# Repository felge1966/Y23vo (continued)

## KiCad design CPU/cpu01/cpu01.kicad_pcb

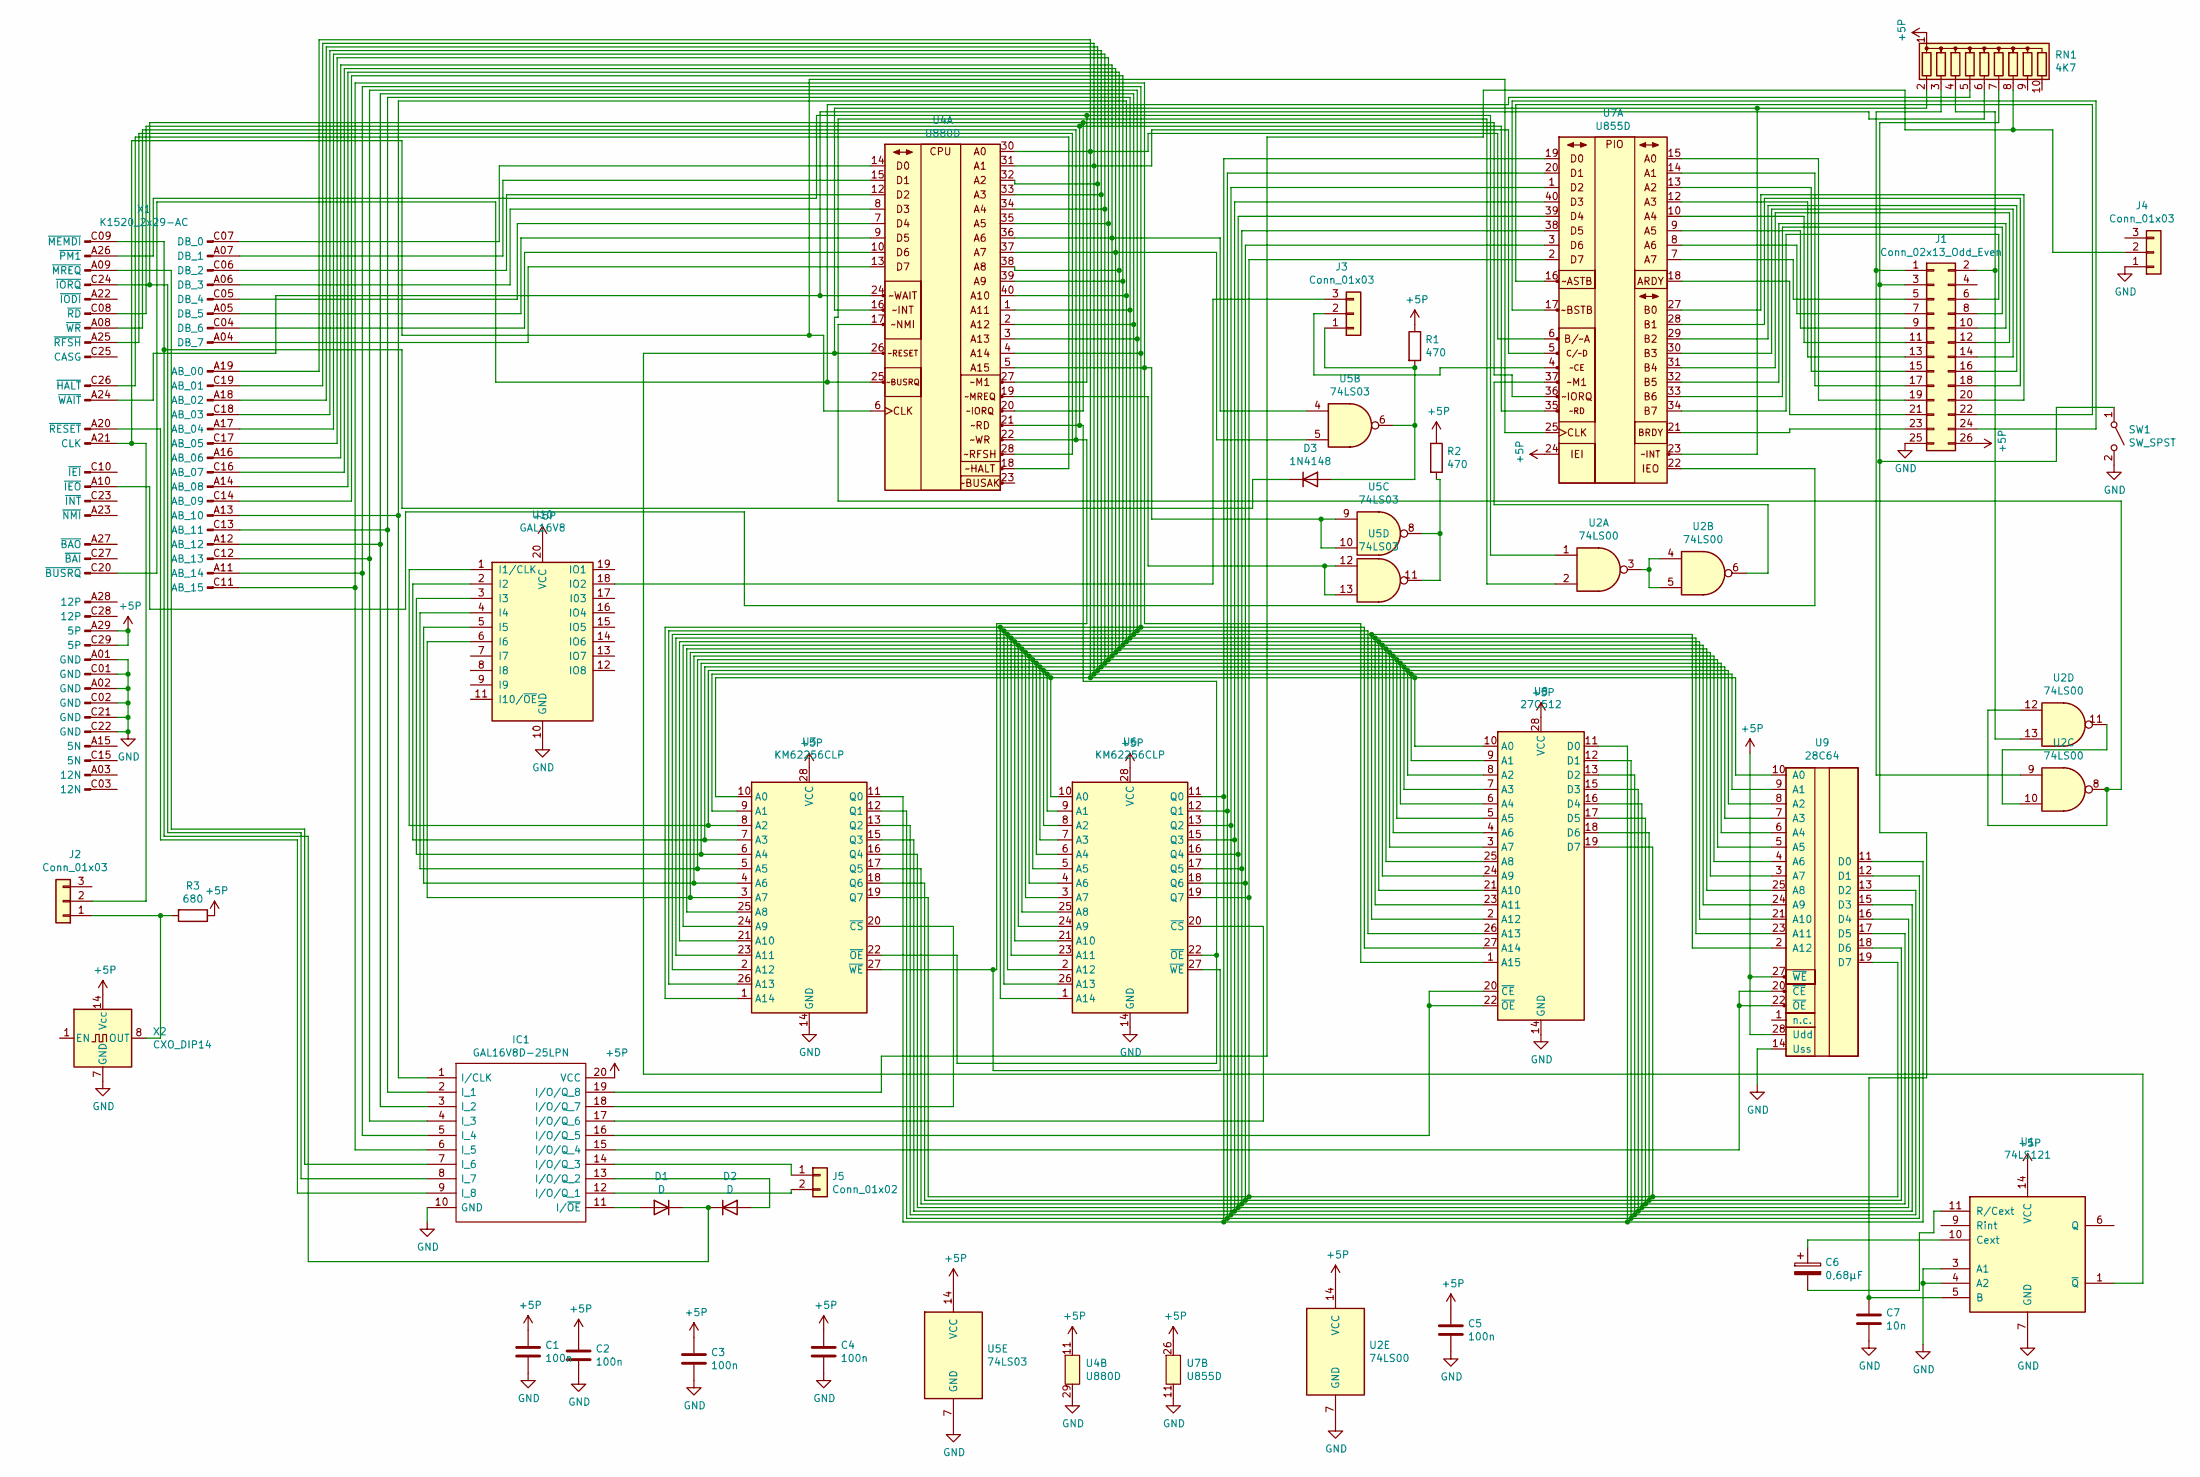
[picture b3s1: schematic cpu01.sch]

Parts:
C1, C2, C3, C4, C5: 100n; C_Disc_D3.0mm_W2.0mm_P2.50mm
C6: 0,68µF; CP_Radial_D4.0mm_P2.00mm
C7: 10n; C_Disc_D3.0mm_W2.0mm_P2.50mm
D1, D2: D; D_DO-15_P10.16mm_Horizontal
D3: 1N4148; D_DO-15_P10.16mm_Horizontal
IC1: GAL16V8D-25LPN; DIP762W56P254L2591H533Q20N; Manufacturer_Part_Number GAL16V8D-25LPN; Mouser Part Number 842-GAL16V8D25LPN
J1: Conn_02x13_Odd_Even; PinSocket_2x13_P2.54mm_Horizontal
J2, J3, J4: Conn_01x03; PinSocket_1x03_P2.54mm_Vertical
J5: Conn_01x02; PinSocket_1x02_P2.54mm_Vertical
R1, R2: 470; R_Axial_DIN0207_L6.3mm_D2.5mm_P10.16mm_Horizontal
R3: 680; R_Axial_DIN0207_L6.3mm_D2.5mm_P10.16mm_Horizontal
RN1: 4K7; R_Array_SIP10
SW1: SW_SPST; SW_Tactile_SKHH_Angled
U1: 74LS121; DIP-14_W7.62mm_LongPads
U2: 74LS00; DIP-14_W7.62mm_LongPads
U3, U6: KM62256CLP; DIP-28_W15.24mm
U4: U880D; DIP-40_W15.24mm_LongPads
U5: 74LS03; DIP-14_W7.62mm_LongPads
U7: U855D; DIP-40_W15.24mm_LongPads
U8: 27C512; DIP-28_W15.24mm
U9: 28C64; DIP-28_W15.24mm_LongPads
U10: GAL16V8; PLCC-20_THT-Socket
X1: K1520_2x29-AC; K1520_EFS2x29_DIN_male
X2: CXO_DIP14; Oscillator_DIP-14

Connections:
+5P: C1.1, C2.1, C3.1, C4.1, C5.1, IC1.20 (VCC), J1.26, R1.1, R2.1, R3.1, RN1.1 (common), U1.14 (VCC), U2.14 (VCC), U3.28 (VCC), U4.11 (Vcc), U5.14 (VCC), U6.28 (VCC), U7.24 (IEI), U7.26 (Vcc), U8.28 (VCC), U9.27 (~WE), U9.28 (Udd), U10.20 (VCC), X1.A29 (5P), X1.C29 (5P), X2.14 (Vcc)
GND: C1.2, C2.2, C3.2, C4.2, C5.2, C7.2, IC1.10 (GND), J1.25, J4.1, SW1.2 (B), U1.3 (A1), U1.4 (A2), U1.7 (GND), U2.7 (GND), U3.14 (GND), U4.29 (GND), U5.7 (GND), U6.14 (GND), U7.11 (GND), U8.14 (GND), U9.14 (Uss), U10.10 (GND), X1.A01 (GND), X1.A02 (GND), X1.C01 (GND), X1.C02 (GND), X1.C21 (GND), X1.C22 (GND), X2.7 (GND)
unnamed: C6.1, U1.10 (Cext)
unnamed: C6.2, U1.11 (R/Cext)
unnamed: C7.1, J1.3, RN1.7 (R6), SW1.1 (A), U1.5 (B)
unnamed: D1.1 (K), D2.1 (K), D3.1 (K), X1.C09 (~MEMDI)
unnamed: D1.2 (A), IC1.11 (I/~OE)
unnamed: D2.2 (A), IC1.13 (I/O/Q_2)
unnamed: D3.2 (A), J3.1, R1.2, U5.6
unnamed: IC1.1 (I/CLK), U3.21 (A10), U4.40 (A10), U6.21 (A10), U8.21 (A10), U9.21 (A10), X1.A13 (AB_10)
unnamed: IC1.2 (I_1), U3.23 (A11), U4.1 (A11), U6.23 (A11), U8.23 (A11), U9.23 (A11), X1.C13 (AB_11)
unnamed: IC1.3 (I_2), U3.2 (A12), U4.2 (A12), U6.2 (A12), U8.2 (A12), U9.2 (A12), X1.A12 (AB_12)
unnamed: IC1.4 (I_3), U3.26 (A13), U4.3 (A13), U6.26 (A13), U8.26 (A13), X1.C12 (AB_13)
unnamed: IC1.5 (I_4), U3.1 (A14), U4.4 (A14), U6.1 (A14), U8.27 (A14), X1.A11 (AB_14)
unnamed: IC1.6 (I_5), U4.5 (A15), U5.9, U5.10, U8.1 (A15), X1.C11 (AB_15)
unnamed: IC1.7 (I_6), X1.A09 (~MREQ)
unnamed: IC1.8 (I_7), U4.20 (~IORQ), U7.36 (~IORQ), X1.C24 (~IORQ)
unnamed: IC1.9 (I_8), X1.A20 (~RESET)
unnamed: IC1.12 (I/O/Q_1), J5.2
unnamed: IC1.14 (I/O/Q_3), J5.1
unnamed: IC1.15 (I/O/Q_4), U9.20 (~CE), U9.22 (~OE)
unnamed: IC1.16 (I/O/Q_5), U8.20 (~CE), U8.22 (~OE)
unnamed: IC1.17 (I/O/Q_6), U6.20 (~CS)
unnamed: IC1.18 (I/O/Q_7), U3.20 (~CS)
unnamed: IC1.19 (I/O/Q_8), J4.2, RN1.8 (R7)
unnamed: J1.1, RN1.3 (R2), U2.9
unnamed: J1.2, RN1.4 (R3), U2.13
unnamed: J1.5, U7.7 (A7)
unnamed: J1.6, U7.34 (B7)
unnamed: J1.7, U7.8 (A6)
unnamed: J1.8, U7.33 (B6)
unnamed: J1.9, U7.9 (A5)
unnamed: J1.10, U7.32 (B5)
unnamed: J1.11, U7.10 (A4)
unnamed: J1.12, U7.31 (B4)
unnamed: J1.13, U7.12 (A3)
unnamed: J1.14, U7.30 (B3)
unnamed: J1.15, U7.13 (A2)
unnamed: J1.16, U7.29 (B2)
unnamed: J1.17, U7.14 (A1)
unnamed: J1.18, U7.28 (B1)
unnamed: J1.19, U7.15 (A0)
unnamed: J1.20, U7.27 (B0)
unnamed: J1.21, U7.18 (ARDY)
unnamed: J1.22, U7.16 (~ASTB)
unnamed: J1.23, U7.21 (BRDY)
unnamed: J1.24, U7.17 (~BSTB)
unnamed: J2.1, R3.2, X2.8 (OUT)
unnamed: J2.2, U4.6 (CLK), U7.25 (CLK), X1.A21 (CLK)
unnamed: J3.2, U7.4 (~CE)
unnamed: J3.3, U10.18 (IO2)
unnamed: R2.2, U5.8, U5.11
unnamed: RN1.2 (R1), U4.16 (~INT), U7.23 (~INT)
unnamed: RN1.5 (R4), U4.25 (~BUSRQ), X1.C20 (~BUSRQ)
unnamed: RN1.6 (R5), U4.24 (~WAIT), X1.A24 (~WAIT)
unnamed: U1.1 (~Q), U2.2, U4.26 (~RESET)
unnamed: U2.1, U4.27 (~M1), X1.A26 (~PM1)
unnamed: U2.3, U2.4, U2.5
unnamed: U2.6, U7.37 (~M1)
unnamed: U2.10, U2.11
unnamed: U2.8, U2.12, U4.17 (~NMI)
unnamed: U3.9 (A1), U4.31 (A1), U6.9 (A1), U7.5 (C/~D), U8.9 (A1), U9.9 (A1), X1.C19 (AB_01)
unnamed: U3.10 (A0), U4.30 (A0), U6.10 (A0), U7.6 (B/~A), U8.10 (A0), U9.10 (A0), X1.A19 (AB_00)
unnamed: U3.11 (Q0), U6.11 (Q0), U7.19 (D0), U8.11 (D0), U9.11 (D0)
unnamed: U3.12 (Q1), U6.12 (Q1), U7.20 (D1), U8.12 (D1), U9.12 (D1)
unnamed: U3.13 (Q2), U6.13 (Q2), U7.1 (D2), U8.13 (D2), U9.13 (D2)
unnamed: U3.15 (Q3), U6.15 (Q3), U7.40 (D3), U8.15 (D3), U9.15 (D3)
unnamed: U3.16 (Q4), U6.16 (Q4), U7.39 (D4), U8.16 (D4), U9.16 (D4)
unnamed: U3.17 (Q5), U6.17 (Q5), U7.38 (D5), U8.17 (D5), U9.17 (D5)
unnamed: U3.18 (Q6), U6.18 (Q6), U7.3 (D6), U8.18 (D6), U9.18 (D6)
unnamed: U3.19 (Q7), U6.19 (Q7), U7.2 (D7), U8.19 (D7), U9.19 (D7)
unnamed: U3.22 (~OE), U4.21 (~RD), U6.22 (~OE), U7.35 (~RD), X1.C08 (~RD)
unnamed: U3.24 (A9), U4.39 (A9), U6.24 (A9), U8.24 (A9), U9.24 (A9), X1.C14 (AB_09)
unnamed: U3.25 (A8), U4.38 (A8), U6.25 (A8), U8.25 (A8), U9.25 (A8), X1.A14 (AB_08)
unnamed: U3.27 (~WE), U4.22 (~WR), U6.27 (~WE), X1.A08 (~WR)
unnamed: U4.7 (D4), X1.C05 (DB_4)
unnamed: U4.8 (D3), X1.A06 (DB_3)
unnamed: U4.9 (D5), X1.A05 (DB_5)
unnamed: U4.10 (D6), X1.C04 (DB_6)
unnamed: U4.12 (D2), X1.C06 (DB_2)
unnamed: U4.13 (D7), X1.A04 (DB_7)
unnamed: U4.14 (D0), X1.C07 (DB_0)
unnamed: U4.15 (D1), X1.A07 (DB_1)
unnamed: U4.18 (~HALT), X1.C26 (~HALT)
unnamed: U4.19 (~MREQ), U5.12, U5.13
unnamed: U4.28 (~RFSH), X1.A25 (~RFSH)
unnamed: U7.22 (IEO), X1.A10 (~IEO)
unnamed: U3.8 (A2), U4.32 (A2), U6.8 (A2), U8.8 (A2), U9.8 (A2), U10.1 (I1/CLK), X1.A18 (AB_02)
unnamed: U3.7 (A3), U4.33 (A3), U6.7 (A3), U8.7 (A3), U9.7 (A3), U10.2 (I2), X1.C18 (AB_03)
unnamed: U3.6 (A4), U4.34 (A4), U6.6 (A4), U8.6 (A4), U9.6 (A4), U10.3 (I3), X1.A17 (AB_04)
unnamed: U3.5 (A5), U4.35 (A5), U6.5 (A5), U8.5 (A5), U9.5 (A5), U10.4 (I4), X1.C17 (AB_05)
unnamed: U3.4 (A6), U4.36 (A6), U5.4, U6.4 (A6), U8.4 (A6), U9.4 (A6), U10.5 (I5), X1.A16 (AB_06)
unnamed: U3.3 (A7), U4.37 (A7), U5.5, U6.3 (A7), U8.3 (A7), U9.3 (A7), U10.6 (I6), X1.C16 (AB_07)

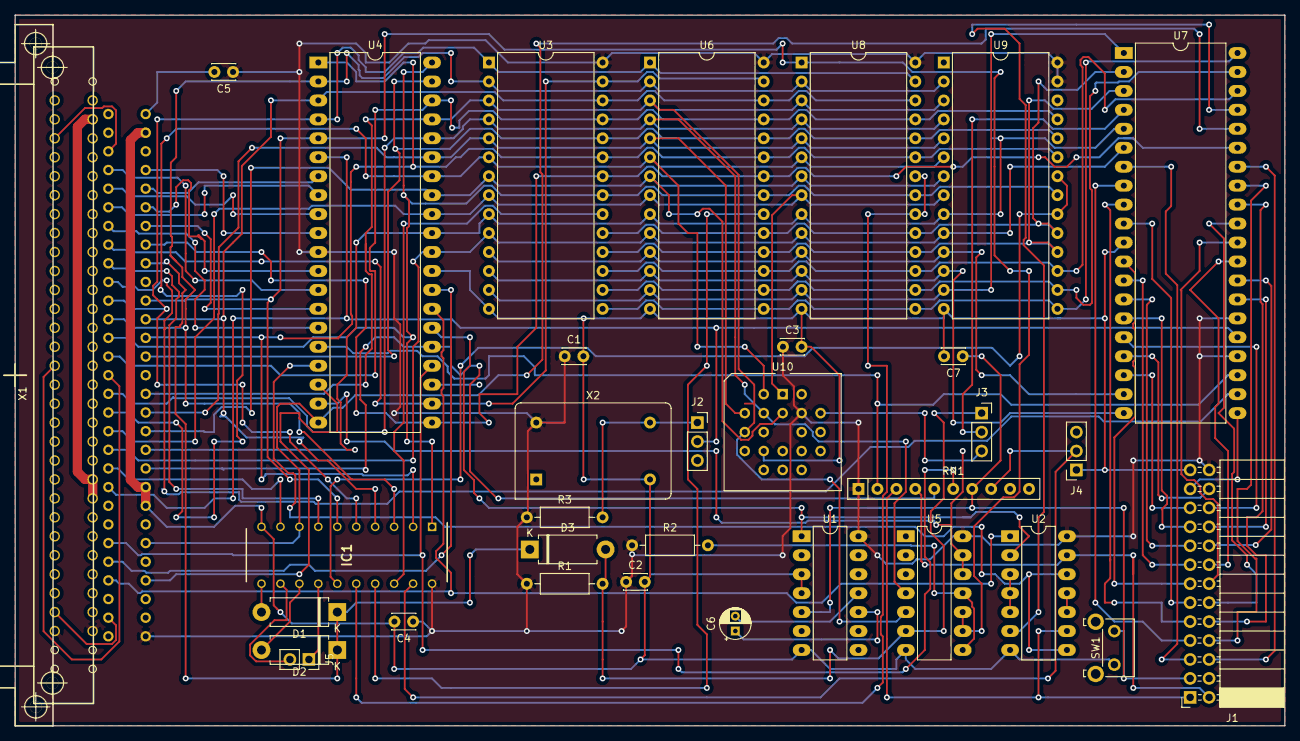
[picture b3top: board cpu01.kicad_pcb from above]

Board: 2 copper layers, 170.2 x 95.2 mm, 33 parts (0 on the bottom side), 93 nets.

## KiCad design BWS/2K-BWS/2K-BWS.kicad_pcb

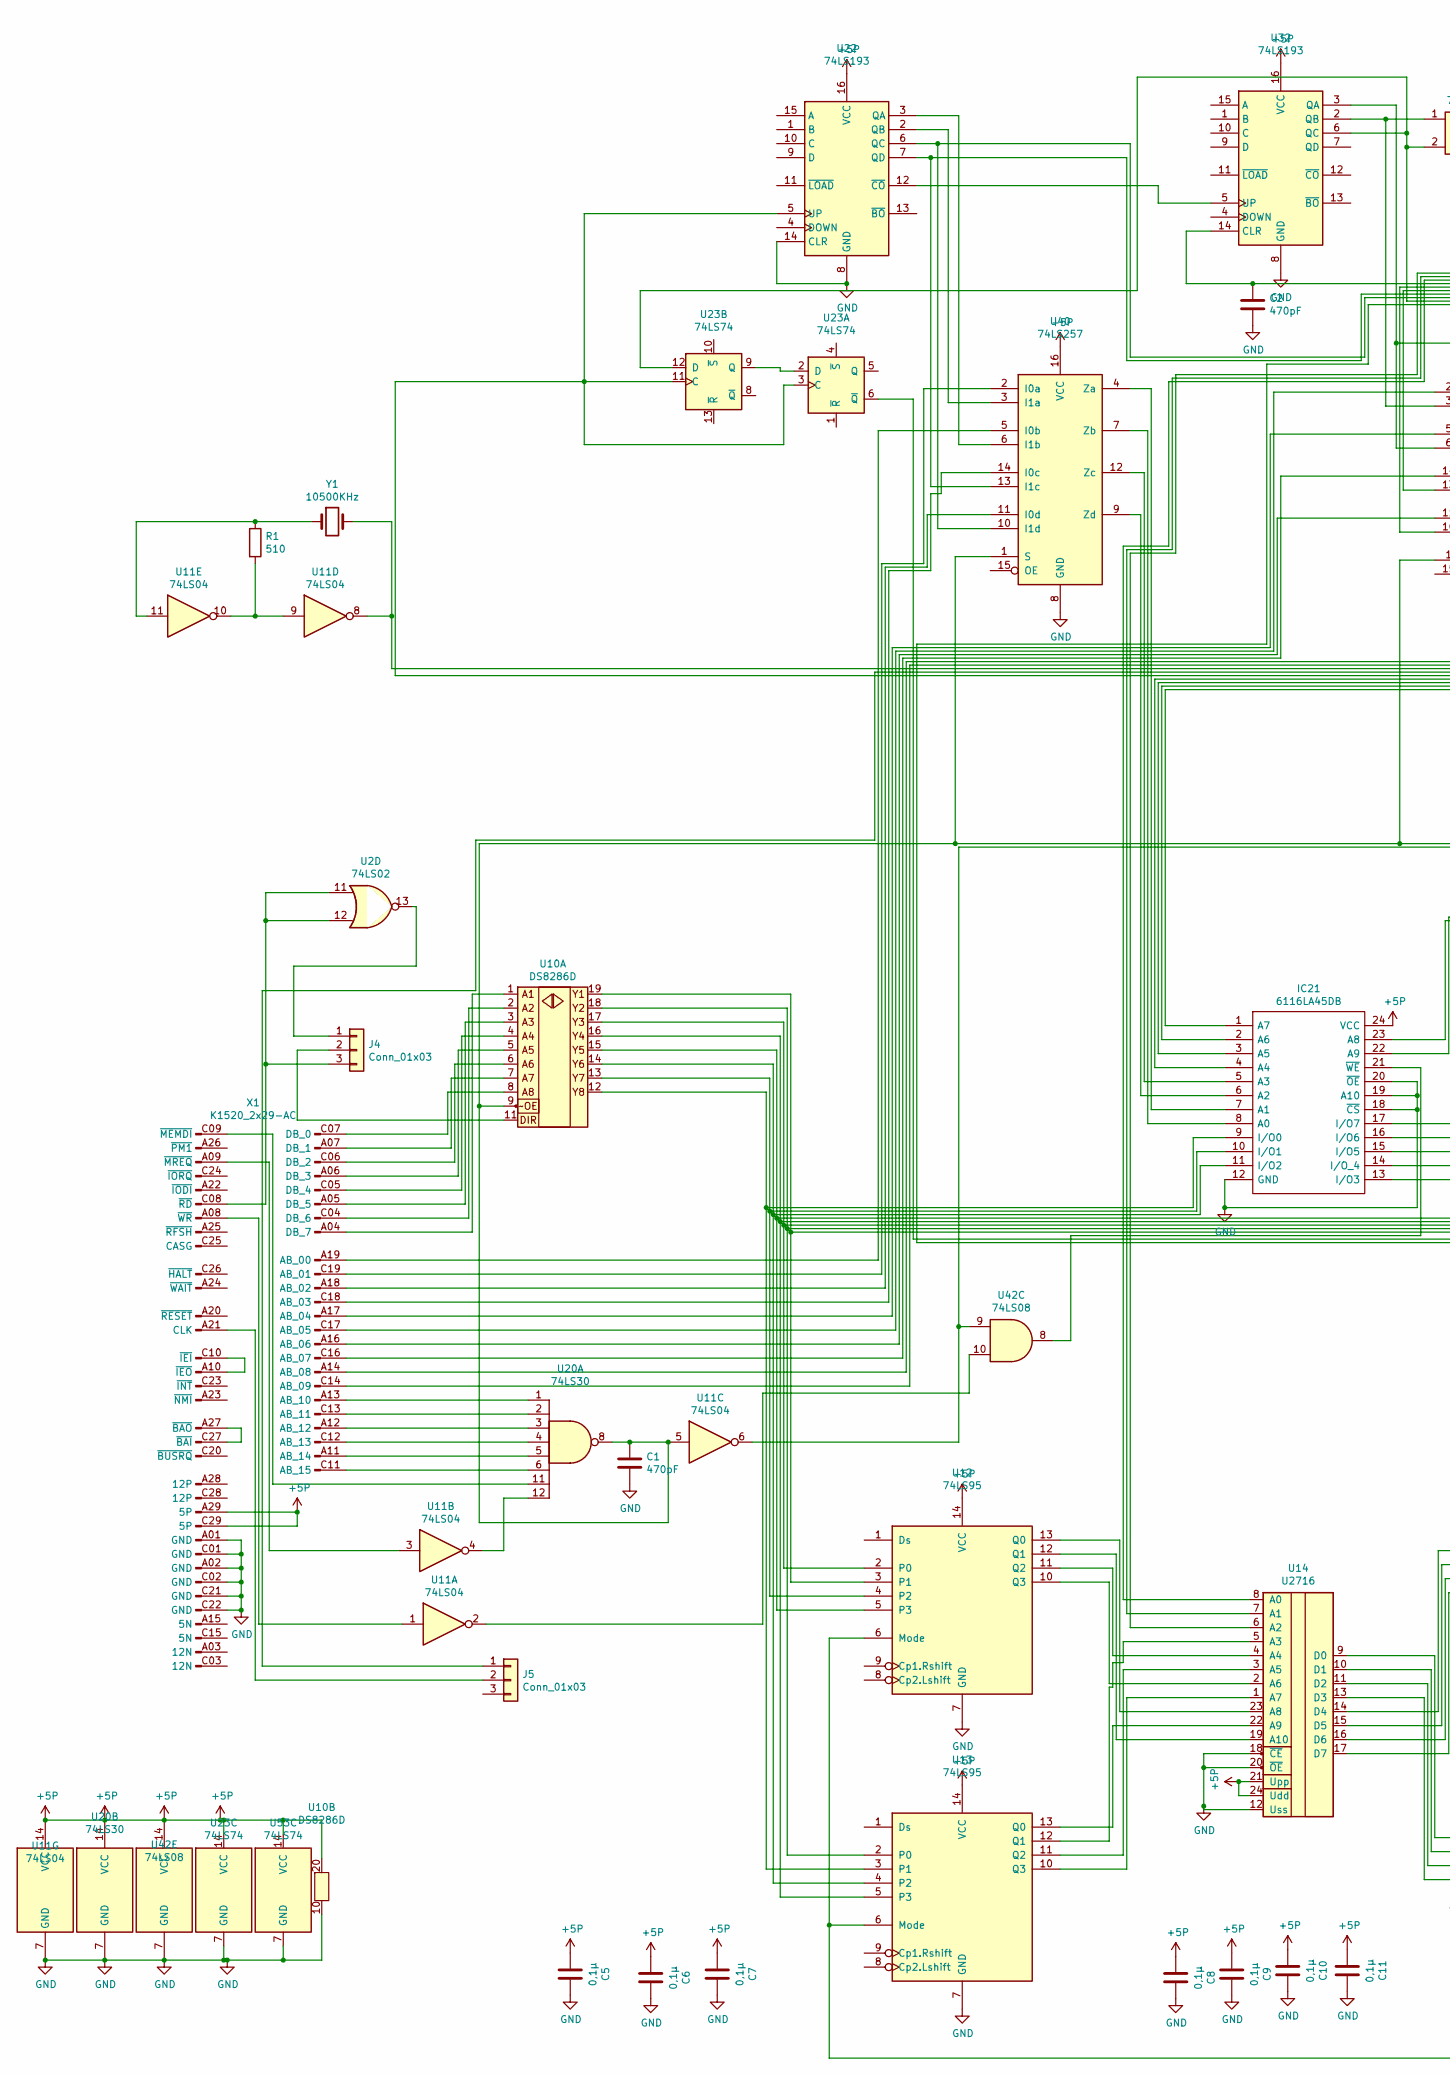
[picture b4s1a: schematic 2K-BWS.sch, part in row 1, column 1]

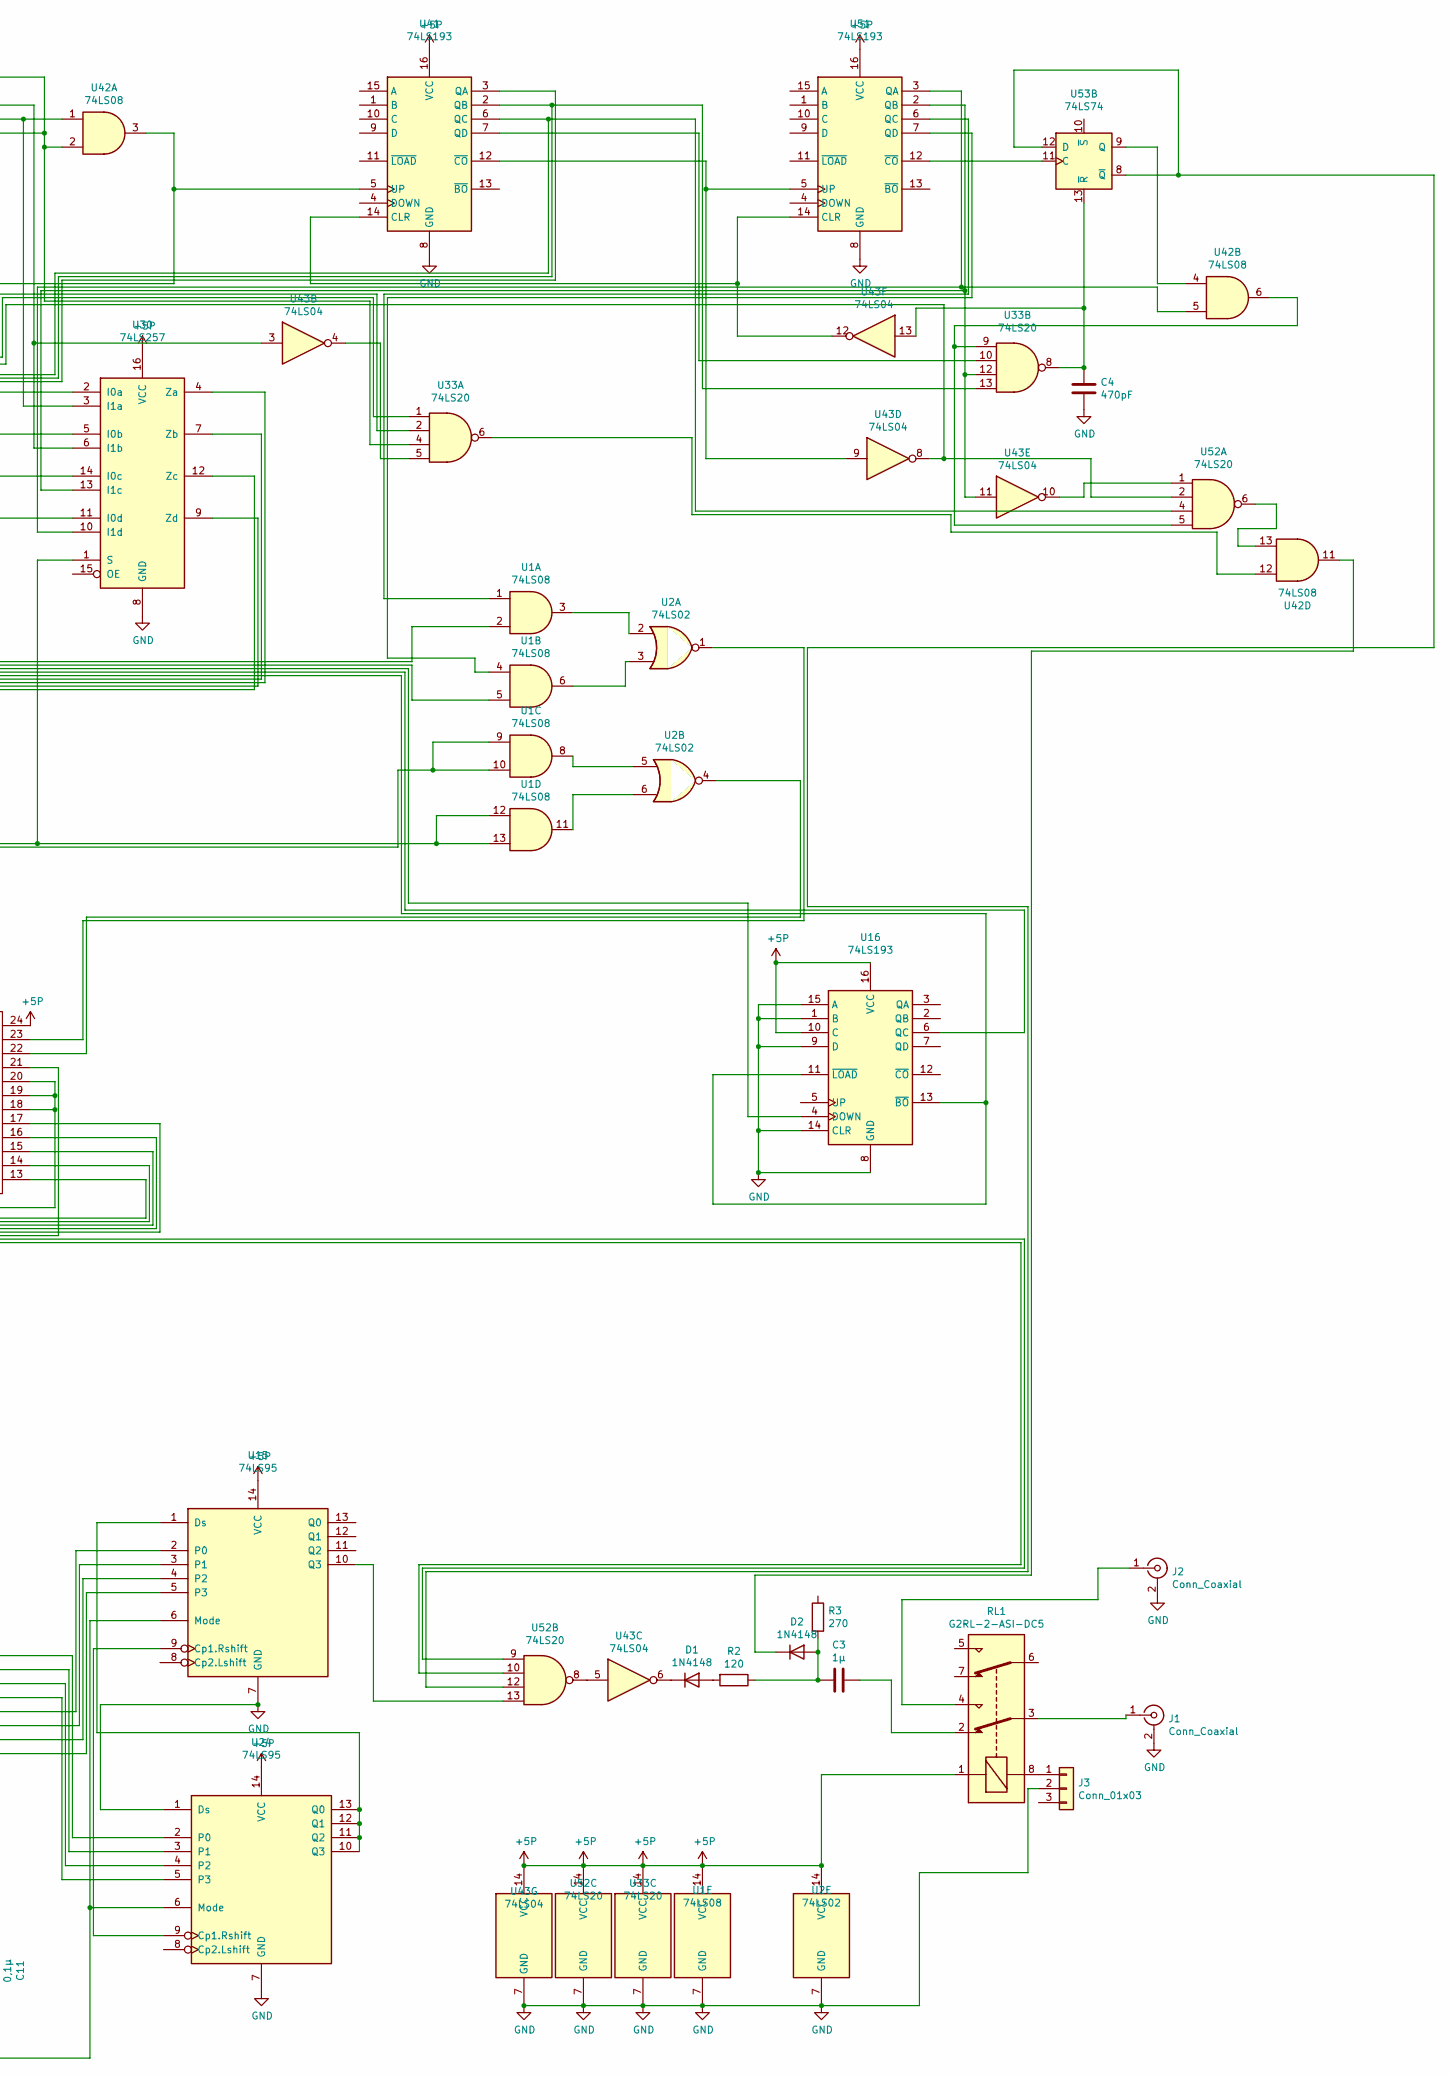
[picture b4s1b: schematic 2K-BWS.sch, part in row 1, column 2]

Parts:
C1, C2, C4: 470pF; C_Disc_D3.0mm_W2.0mm_P2.50mm
C3: 1µ; C_Disc_D3.0mm_W2.0mm_P2.50mm
C5, C6, C7, C8, C9, C10, C11: 0,1µ; C_Disc_D3.0mm_W2.0mm_P2.50mm
D1, D2: 1N4148; D_DO-15_P10.16mm_Horizontal
IC21: 6116LA45DB; DIP-24_W15.24mm_LongPads; Manufacturer_Part_Number 6116LA45DB; Mouser Part Number 972-6116LA45DB
J1, J2: Conn_Coaxial; chinch
J3, J4, J5: Conn_01x03; PinSocket_1x03_P2.54mm_Vertical
R1: 510; R_Axial_DIN0207_L6.3mm_D2.5mm_P10.16mm_Horizontal
R2: 120; R_Axial_DIN0207_L6.3mm_D2.5mm_P10.16mm_Horizontal
R3: 270; R_Axial_DIN0207_L6.3mm_D2.5mm_P10.16mm_Horizontal
RL1: G2RL-2-ASI-DC5; Relay_DPDT_Omron_G2RL
U1, U42: 74LS08; DIP-14_W7.62mm_LongPads
U2: 74LS02; DIP-14_W7.62mm_LongPads
U10: DS8286D; DIP-20_W7.62mm_LongPads
U11, U43: 74LS04; DIP-14_W7.62mm_LongPads
U12, U13, U15, U24: 74LS95; DIP-14_W7.62mm_LongPads
U14: U2716; DIP-24_W15.24mm_LongPads
U16, U22, U32, U41, U51: 74LS193; DIP-16_W7.62mm_LongPads
U20: 74LS30; DIP-14_W7.62mm_LongPads
U23, U53: 74LS74; DIP-14_W7.62mm_LongPads
U30, U40: 74LS257; DIP-16_W7.62mm_LongPads
U33, U52: 74LS20; DIP-14_W7.62mm_LongPads
X1: K1520_2x29-AC; K1520_EFS2x29_DIN_male
Y1: 10500KHz; Crystal_HC49-4H_Vertical

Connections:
+5P: C5.2, C6.2, C7.2, C8.2, C9.2, C10.2, C11.2, IC21.24 (VCC), RL1.1, U1.14 (VCC), U2.14 (VCC), U10.20 (Vcc), U11.14 (VCC), U12.14 (VCC), U13.14 (VCC), U14.21 (Upp), U14.24 (Udd), U15.14 (VCC), U16.10 (C), U16.16 (VCC), U20.14 (VCC), U22.16 (VCC), U23.14 (VCC), U24.14 (VCC), U30.16 (VCC), U32.16 (VCC), U33.14 (VCC), U40.16 (VCC), U41.16 (VCC), U42.14 (VCC), U43.14 (VCC), U51.16 (VCC), U52.14 (VCC), U53.14 (VCC), X1.A29 (5P), X1.C29 (5P)
GND: C1.2, C2.2, C4.2, C5.1, C6.1, C7.1, C8.1, C9.1, C10.1, C11.1, IC21.12 (GND), IC21.18 (~CS), IC21.19 (A10), IC21.20 (~OE), J1.2 (Ext), J2.2 (Ext), J3.2, U1.7 (GND), U2.7 (GND), U10.10 (GND), U11.7 (GND), U12.7 (GND), U13.7 (GND), U14.12 (Uss), U14.18 (~CE), U14.20 (~OE), U15.7 (GND), U16.1 (B), U16.8 (GND), U16.9 (D), U16.14 (CLR), U16.15 (A), U20.7 (GND), U22.8 (GND), U22.14 (CLR), U23.7 (GND), U24.1 (Ds), U24.7 (GND), U30.8 (GND), U32.8 (GND), U33.7 (GND), U40.8 (GND), U41.8 (GND), U42.7 (GND), U43.7 (GND), U51.8 (GND), U52.7 (GND), U53.7 (GND), X1.A01 (GND), X1.A02 (GND), X1.C01 (GND), X1.C02 (GND), X1.C21 (GND), X1.C22 (GND)
unnamed: C1.1, U1.12, U1.13, U10.9 (~OE), U11.5, U20.8, U30.1 (S), U40.1 (S)
unnamed: C2.1, U32.14 (CLR), U41.5 (UP), U42.3
unnamed: C3.1, RL1.2
unnamed: C3.2, D2.2 (A), R2.1, R3.2
unnamed: C4.1, U33.8, U43.13, U53.13 (~R)
unnamed: D1.1 (K), U43.6
unnamed: D1.2 (A), R2.2
unnamed: D2.1 (K), U42.11
unnamed: IC21.1 (A7), U30.12 (Zc)
unnamed: IC21.2 (A6), U30.9 (Zd)
unnamed: IC21.3 (A5), U30.4 (Za)
unnamed: IC21.4 (A4), U30.7 (Zb)
unnamed: IC21.5 (A3), U40.12 (Zc)
unnamed: IC21.6 (A2), U40.9 (Zd)
unnamed: IC21.7 (A1), U40.4 (Za)
unnamed: IC21.8 (A0), U40.7 (Zb)
unnamed: IC21.9 (I/O0), U10.12 (Y8), U13.3 (P1)
unnamed: IC21.10 (I/O1), U10.13 (Y7), U12.4 (P2)
unnamed: IC21.11 (I/O2), U10.14 (Y6), U13.4 (P2)
unnamed: IC21.13 (I/O3), U10.15 (Y5), U12.5 (P3)
unnamed: IC21.14 (I/O_4), U10.16 (A4), U13.5 (P3)
unnamed: IC21.15 (I/O5), U10.17 (Y3), U12.2 (P0)
unnamed: IC21.16 (I/O6), U10.18 (Y2), U13.2 (P0)
unnamed: IC21.17 (I/O7), U10.19 (Y1), U12.3 (P1)
unnamed: IC21.21 (~WE), U42.8
unnamed: IC21.22 (A9), U2.4
unnamed: IC21.23 (A8), U2.1
unnamed: J1.1 (In), RL1.3
unnamed: J2.1 (In), RL1.4
unnamed: J3.1, RL1.8
unnamed: J4.1, U2.13
unnamed: J4.2, U10.11 (STB)
unnamed: J4.3, U2.11, U2.12, X1.C08 (~RD)
unnamed: J5.1, U16.6 (QC)
unnamed: J5.2, X1.A21 (CLK)
unnamed: R1.1, U11.11, Y1.1
unnamed: R1.2, U11.9, U11.10
unnamed: U1.1, U51.6 (QC)
unnamed: U1.2, X1.A14 (AB_08)
unnamed: U1.3, U2.2
unnamed: U1.4, U51.7 (QD)
unnamed: U1.5, X1.C14 (AB_09)
unnamed: U1.6, U2.3
unnamed: U1.8, U2.5
unnamed: U1.9, U1.10, U11.6, U42.9
unnamed: U1.11, U2.6
unnamed: U10.1 (A1), X1.A04 (DB_7)
unnamed: U10.2 (A2), X1.C04 (DB_6)
unnamed: U10.3 (A3), X1.A05 (DB_5)
unnamed: U10.4 (A4), X1.C05 (DB_4)
unnamed: U10.5 (A5), X1.A06 (DB_3)
unnamed: U10.6 (A6), X1.C06 (DB_2)
unnamed: U10.7 (A7), X1.A07 (DB_1)
unnamed: U10.8 (A8), X1.C07 (DB_0)
unnamed: U11.1, X1.A08 (~WR)
unnamed: U11.2, U42.10
unnamed: U11.3, X1.A09 (~MREQ)
unnamed: U11.4, U20.12
unnamed: U11.8, U16.4 (DOWN), Y1.2
unnamed: U12.6 (Mode), U13.6 (Mode), U15.6 (Mode), U24.6 (Mode)
unnamed: U12.10 (Q3), U14.2 (A6)
unnamed: U12.11 (Q2), U14.4 (A4)
unnamed: U12.12 (Q1), U14.19 (A10)
unnamed: U12.13 (Q0), U14.23 (A8)
unnamed: U13.10 (Q3), U14.1 (A7)
unnamed: U13.11 (Q2), U14.3 (A5)
unnamed: U13.12 (Q1), U14.5 (A3)
unnamed: U13.13 (Q0), U14.22 (A9)
unnamed: U14.6 (A2), U41.6 (QC), U52.4
unnamed: U14.7 (A1), U33.13, U41.2 (QB)
unnamed: U14.8 (A0), U41.3 (QA)
unnamed: U14.9 (D0), U24.2 (P0)
unnamed: U14.10 (D1), U24.3 (P1)
unnamed: U14.11 (D2), U24.4 (P2)
unnamed: U14.13 (D3), U24.5 (P3)
unnamed: U14.14 (D4), U15.2 (P0)
unnamed: U14.15 (D5), U15.3 (P1)
unnamed: U14.16 (D6), U15.4 (P2)
unnamed: U14.17 (D7), U15.5 (P3)
unnamed: U15.1 (Ds), U24.10 (Q3), U24.11 (Q2), U24.12 (Q1), U24.13 (Q0)
unnamed: U15.9 (Cp1.Rshift), U24.9 (Cp1.Rshift)
unnamed: U15.10 (Q3), U52.13
unnamed: U16.11 (~LOAD), U16.13 (~BO), U22.5 (UP), U23.3 (C), U23.11 (C)
unnamed: U20.1, X1.A13 (AB_10)
unnamed: U20.2, X1.C13 (AB_11)
unnamed: U20.3, X1.A12 (AB_12)
unnamed: U20.4, X1.C12 (AB_13)
unnamed: U20.5, X1.A11 (AB_14)
unnamed: U20.6, X1.C11 (AB_15)
unnamed: U20.11, X1.C09 (~MEMDI)
unnamed: U22.2 (QB), U40.3 (I1a)
unnamed: U22.3 (QA), U40.6 (I1b)
unnamed: U22.6 (QC), U33.1, U40.10 (I1d)
unnamed: U22.7 (QD), U33.2, U40.13 (I1c)
unnamed: U22.12 (~CO), U32.5 (UP)
unnamed: U23.2 (D), U23.9 (Q)
unnamed: U23.6 (~Q), U52.9
unnamed: U23.12 (D), U32.6 (QC), U33.4, U42.2
unnamed: U30.2 (I0a), X1.C17 (AB_05)
unnamed: U30.3 (I1a), U32.2 (QB), U42.1
unnamed: U30.5 (I0b), X1.A17 (AB_04)
unnamed: U30.6 (I1b), U32.3 (QA), U43.3
unnamed: U30.10 (I1d), U42.5, U51.3 (QA)
unnamed: U30.11 (I0d), X1.A16 (AB_06)
unnamed: U30.13 (I1c), U33.12, U43.11, U51.2 (QB)
unnamed: U30.14 (I0c), X1.C16 (AB_07)
unnamed: U33.5, U43.4
unnamed: U33.6, U42.12
unnamed: U33.9, U42.6, U52.5
unnamed: U33.10, U41.7 (QD)
unnamed: U40.2 (I0a), X1.C19 (AB_01)
unnamed: U40.5 (I0b), X1.A19 (AB_00)
unnamed: U40.11 (I0d), X1.A18 (AB_02)
unnamed: U40.14 (I0c), X1.C18 (AB_03)
unnamed: U41.12 (~CO), U43.9, U51.5 (UP)
unnamed: U41.14 (CLR), U43.12, U51.14 (CLR)
unnamed: U42.4, U53.9 (Q)
unnamed: U42.13, U52.6
unnamed: U43.5, U52.8
unnamed: U43.8, U52.2, U52.10
unnamed: U43.10, U52.1
unnamed: U51.12 (~CO), U53.11 (C)
unnamed: U52.12, U53.8 (~Q), U53.12 (D)
unnamed: X1.A10 (~IEO), X1.C10 (~IEI)
unnamed: X1.A27 (~BAO), X1.C27 (~BAI)

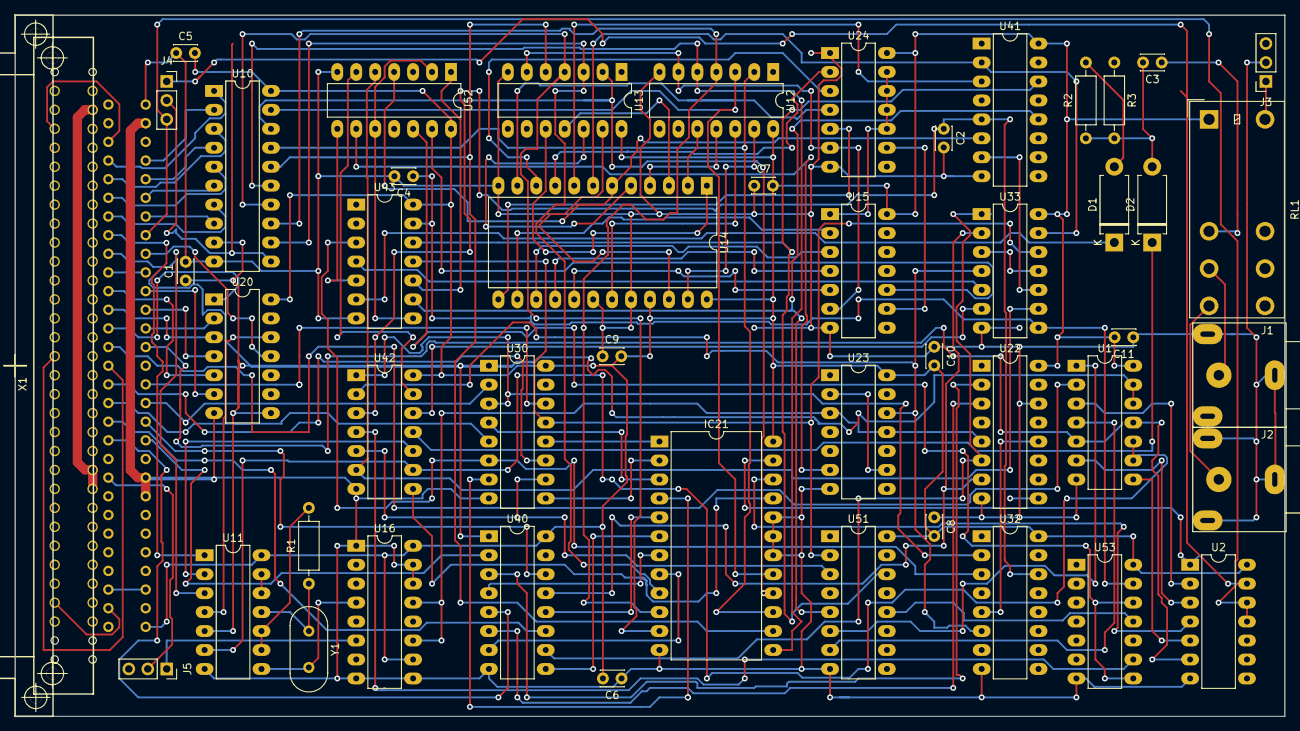
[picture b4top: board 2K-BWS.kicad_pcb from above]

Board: 2 copper layers, 170.2 x 94.0 mm, 48 parts (0 on the bottom side), 127 nets.

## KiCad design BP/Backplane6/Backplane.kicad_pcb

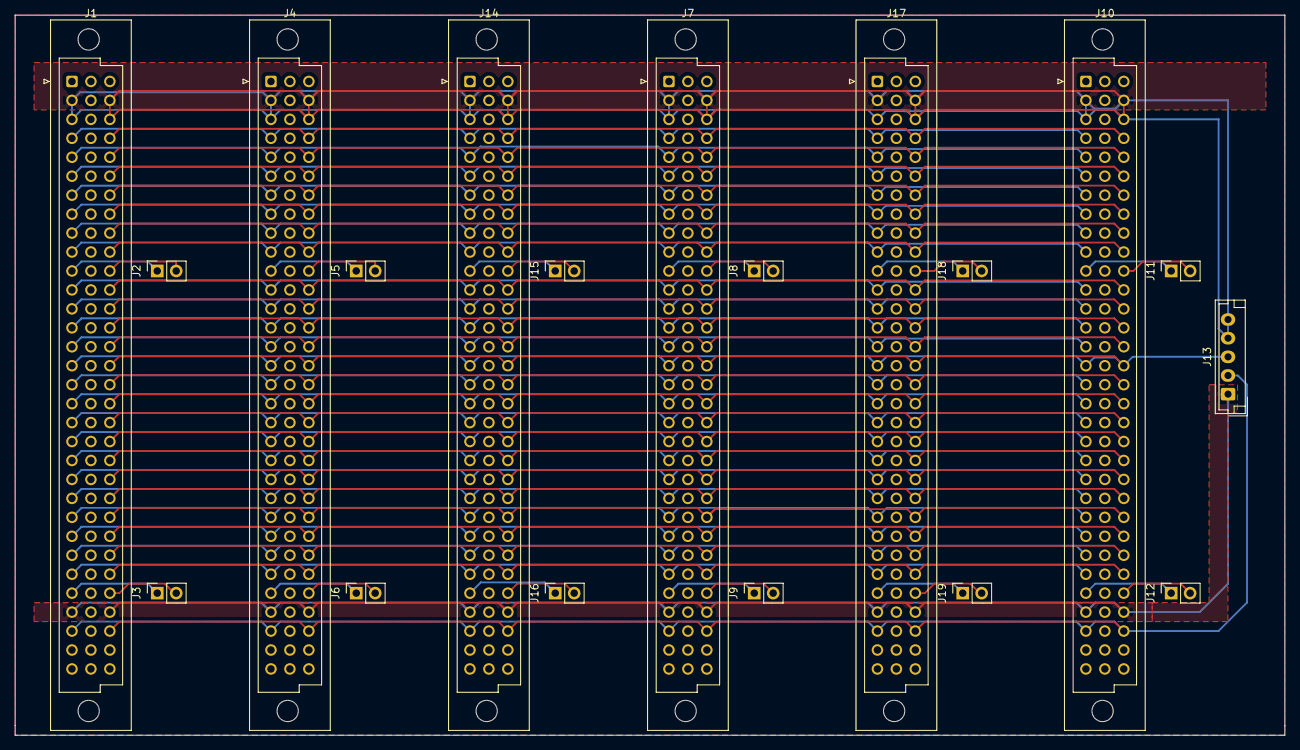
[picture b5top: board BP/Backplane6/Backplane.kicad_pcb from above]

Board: 2 copper layers, 170.2 x 96.5 mm, 19 parts (0 on the bottom side), 72 nets.

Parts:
J1, J4, J7, J10, J14, J17: C64AC; DIN41612_C_3x32_Female_Vertical_THT-Gross
J2, J3, J5, J6, J8, J9, J11, J12, J15, J16, J18, J19: Conn_01x02; PinSocket_1x02_P2.54mm_Vertical
J13: Screw_Terminal_01x05; JST_EH_B5B-EH-A_1x05_P2.50mm_Vertical

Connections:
+5P: J1.A30, J1.C30, J4.A30, J4.C30, J7.A30, J7.C30, J10.A30, J10.C30, J13.2, J14.A30, J14.C30, J17.A30, J17.C30
+12P: J1.A29, J1.C29, J4.A29, J4.C29, J7.A29, J7.C29, J10.A29, J10.C29, J13.1, J14.A29, J14.C29, J17.A29, J17.C29
-5V: J1.A16, J1.C16, J4.A16, J4.C16, J7.A16, J7.C16, J10.A16, J10.C16, J13.3, J14.A16, J14.C16, J17.A16, J17.C16
GND: J1.A2, J1.A3, J1.C2, J1.C3, J4.A2, J4.A3, J4.C2, J4.C3, J7.A2, J7.A3, J7.C2, J7.C3, J10.A2, J10.A3, J10.C2, J10.C3, J13.4, J13.5, J14.A2, J14.A3, J14.C2, J14.C3, J17.A2, J17.A3, J17.C2, J17.C3
unnamed: J1.A4, J4.A4, J7.A4, J10.A4, J14.A4, J17.A4
unnamed: J1.A5, J4.A5, J7.A5, J10.A5, J14.A5, J17.A5
unnamed: J1.A6, J4.A6, J7.A6, J10.A6, J14.A6, J17.A6
unnamed: J1.A7, J4.A7, J7.A7, J10.A7, J14.A7, J17.A7
unnamed: J1.A8, J4.A8, J7.A8, J10.A8, J14.A8, J17.A8
unnamed: J1.A9, J4.A9, J7.A9, J10.A9, J14.A9, J17.A9
unnamed: J1.A10, J4.A10, J7.A10, J10.A10, J14.A10, J17.A10
unnamed: J1.A11, J2.1
unnamed: J1.A12, J4.A12, J7.A12, J10.A12, J14.A12, J17.A12
unnamed: J1.A13, J4.A13, J7.A13, J10.A13, J14.A13, J17.A13
unnamed: J1.A14, J4.A14, J7.A14, J10.A14, J14.A14, J17.A14
unnamed: J1.A15, J4.A15, J7.A15, J10.A15, J14.A15, J17.A15
unnamed: J1.A17, J4.A17, J7.A17, J10.A17, J14.A17, J17.A17
unnamed: J1.A18, J4.A18, J7.A18, J10.A18, J14.A18, J17.A18
unnamed: J1.A19, J4.A19, J7.A19, J10.A19, J14.A19, J17.A19
unnamed: J1.A20, J4.A20, J7.A20, J10.A20, J14.A20, J17.A20
unnamed: J1.A21, J4.A21, J7.A21, J10.A21, J14.A21, J17.A21
unnamed: J1.A22, J4.A22, J7.A22, J10.A22, J14.A22, J17.A22
unnamed: J1.A23, J4.A23, J7.A23, J10.A23, J14.A23, J17.A23
unnamed: J1.A24, J4.A24, J7.A24, J10.A24, J14.A24, J17.A24
unnamed: J1.A25, J4.A25, J7.A25, J10.A25, J14.A25, J17.A25
unnamed: J1.A26, J4.A26, J7.A26, J10.A26, J14.A26, J17.A26
unnamed: J1.A27, J4.A27, J7.A27, J10.A27, J14.A27, J17.A27
unnamed: J1.A28, J3.1
unnamed: J1.C4, J4.C4, J7.C4, J10.C4, J14.C4, J17.C4
unnamed: J1.C5, J4.C5, J7.C5, J10.C5, J14.C5, J17.C5
unnamed: J1.C6, J4.C6, J7.C6, J10.C6, J14.C6, J17.C6
unnamed: J1.C7, J4.C7, J7.C7, J10.C7, J14.C7, J17.C7
unnamed: J1.C8, J4.C8, J7.C8, J10.C8, J14.C8, J17.C8
unnamed: J1.C9, J4.C9, J7.C9, J10.C9, J14.C9, J17.C9
unnamed: J1.C10, J4.C10, J7.C10, J10.C10, J14.C10, J17.C10
unnamed: J1.C11, J2.2
unnamed: J1.C12, J4.C12, J7.C12, J10.C12, J14.C12, J17.C12
unnamed: J1.C13, J4.C13, J7.C13, J10.C13, J14.C13, J17.C13
unnamed: J1.C14, J4.C14, J7.C14, J10.C14, J14.C14, J17.C14
unnamed: J1.C15, J4.C15, J7.C15, J10.C15, J14.C15, J17.C15
unnamed: J1.C17, J4.C17, J7.C17, J10.C17, J14.C17, J17.C17
unnamed: J1.C18, J4.C18, J7.C18, J10.C18, J14.C18, J17.C18
unnamed: J1.C19, J4.C19, J7.C19, J10.C19, J14.C19, J17.C19
unnamed: J1.C20, J4.C20, J7.C20, J10.C20, J14.C20, J17.C20
unnamed: J1.C21, J4.C21, J7.C21, J10.C21, J14.C21, J17.C21
unnamed: J1.C22, J4.C22, J7.C22, J10.C22, J14.C22, J17.C22
unnamed: J1.C23, J4.C23, J7.C23, J10.C23, J14.C23, J17.C23
unnamed: J1.C24, J4.C24, J7.C24, J10.C24, J14.C24, J17.C24
unnamed: J1.C25, J4.C25, J7.C25, J10.C25, J14.C25, J17.C25
unnamed: J1.C26, J4.C26, J7.C26, J10.C26, J14.C26, J17.C26
unnamed: J1.C27, J4.C27, J7.C27, J10.C27, J14.C27, J17.C27
unnamed: J1.C28, J3.2
unnamed: J4.A11, J5.1
unnamed: J4.A28, J6.1
unnamed: J4.C11, J5.2
unnamed: J4.C28, J6.2
unnamed: J7.A11, J8.1
unnamed: J7.A28, J9.1
unnamed: J7.C11, J8.2
unnamed: J7.C28, J9.2
unnamed: J10.A11, J11.1
unnamed: J10.A28, J12.1
unnamed: J10.C11, J11.2
unnamed: J10.C28, J12.2
unnamed: J14.A11, J15.1
unnamed: J14.A28, J16.1
unnamed: J14.C11, J15.2
unnamed: J14.C28, J16.2
unnamed: J17.A11, J18.1
unnamed: J17.A28, J19.1
unnamed: J17.C11, J18.2
unnamed: J17.C28, J19.2
